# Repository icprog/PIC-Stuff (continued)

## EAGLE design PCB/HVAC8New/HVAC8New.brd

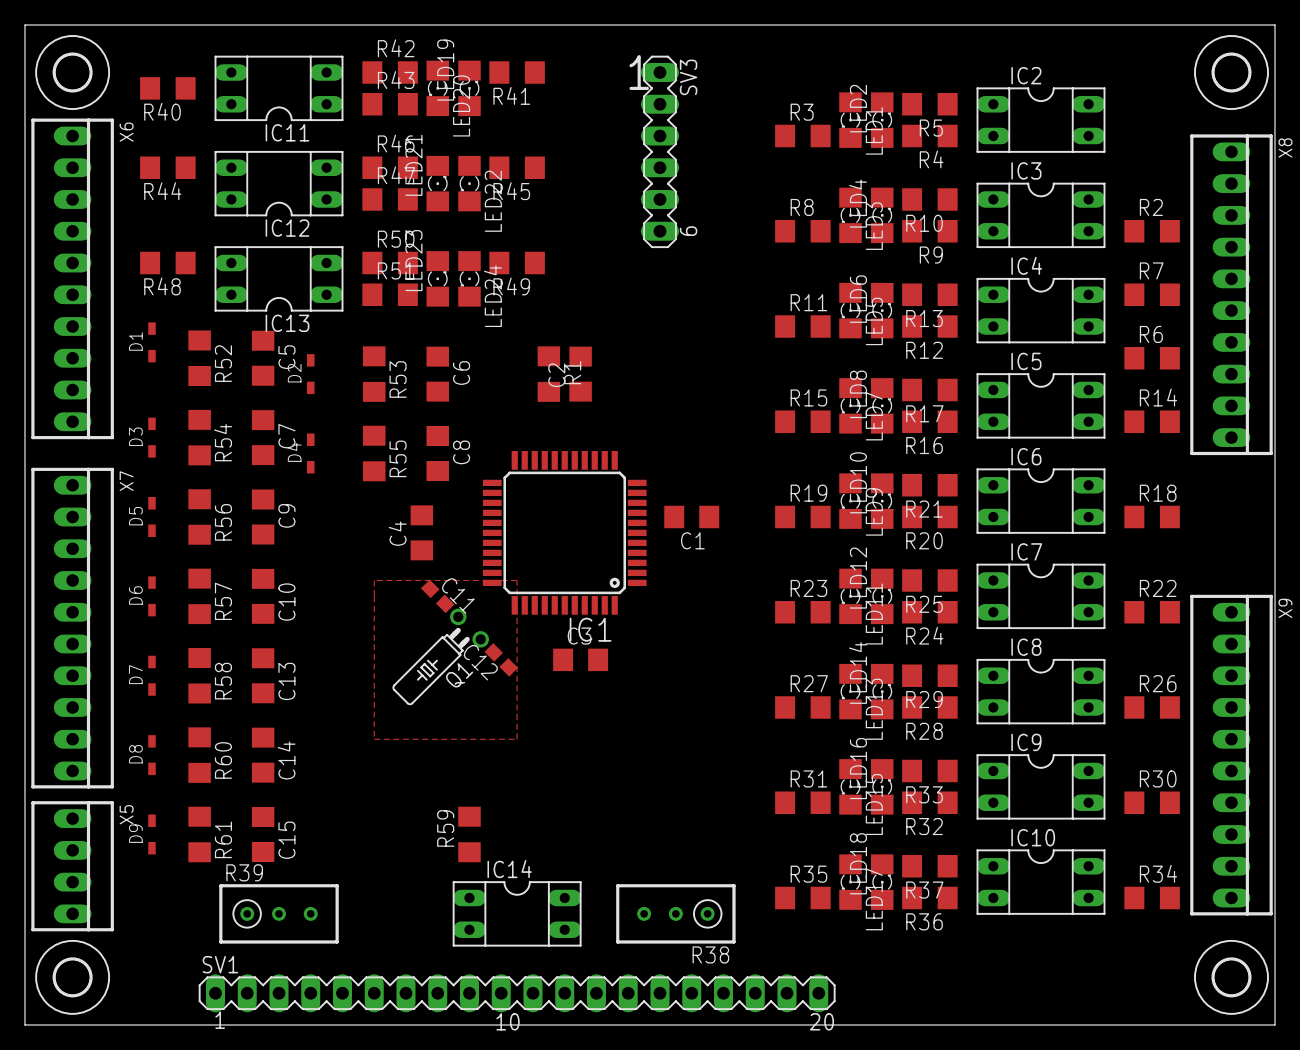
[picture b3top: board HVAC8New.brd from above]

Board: 2 copper layers, 100.0 x 80.0 mm, 135 parts (0 on the bottom side), 104 nets, no tracks yet.

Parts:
C1, C5, C6, C7, C8, C9, C10, C13, C14, C15: 10uf; C1206
C2, C3, C4: .1uf; C1206
C11, C12: 12pf; C0603
D1, D2, D3, D4, D5, D6, D7, D8, D9: 5.1V; SOD323
H1, H2, H3, H4: MOUNT-HOLE2.8; 2,8
IC1: PIC24FV16KM204; TQFP44
IC2, IC3, IC4, IC5, IC6, IC7, IC8, IC9, IC10, IC11, IC12, IC13, IC14: SOCKET-04
LED1, LED3, LED5, LED7, LED9, LED11, LED13, LED15, LED17, LED19, LED21, LED23: Red; LED_1206
LED2, LED4, LED6, LED8, LED10, LED12, LED14, LED16, LED18, LED20, LED22, LED24: Green; LED_1206
Q1: 32.768KHz; TC26H
R1: 10K; R1206
R2, R6, R7, R14, R18, R22, R26, R30, R34, R40, R44, R48: 0R; R1206
R3, R8, R11, R15, R19, R23, R27, R31, R35, R41, R45, R49, R59: 680R; R1206
R4, R5, R9, R10, R12, R13, R16, R17, R20, R21, R24, R25, R28, R29, R32, R33, R36, R37, R42, R43, R46, R47, R50, R51: 330R; R1206
R38, R39: 10K; RTRIM3296W
R52, R53, R54, R55, R56, R57, R58, R60, R61: 250R; R1206
SV1: LCD&Touch; MA20-1
SV3: Program; MA06-1
X5: 22-23-2041
X6, X7, X8, X9: 22-23-2101

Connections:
unnamed: IC13.1, R51.1
unnamed: IC1.18, R1.2, SV3.1
unnamed: IC2.1, R5.1
unnamed: IC1.12, LED7.A, LED8.C, R17.2
unnamed: IC2.4, X8.3
unnamed: LED1.C, LED2.A, R3.2, R4.2
unnamed: IC2.3, R2.1
unnamed: IC3.1, R10.1
unnamed: R2.2, X8.4
unnamed: IC3.4, X8.5
unnamed: LED3.C, LED4.A, R8.2, R9.2
unnamed: IC3.3, R7.1
unnamed: IC11.1, R43.1
unnamed: R7.2, X8.6
unnamed: IC4.1, R13.1
unnamed: LED5.C, LED6.A, R11.2, R12.2
unnamed: IC4.3, R6.1
unnamed: LED19.C, LED20.A, R41.2, R42.2
unnamed: R14.2, X8.10
unnamed: IC5.4, X8.9
unnamed: IC5.1, R17.1
unnamed: LED7.C, LED8.A, R15.2, R16.2
unnamed: IC5.3, R14.1
unnamed: IC6.1, R21.1
unnamed: LED9.C, LED10.A, R19.2, R20.2
unnamed: IC6.3, R18.1
unnamed: R6.2, X8.8
unnamed: IC4.4, X8.7
unnamed: IC11.3, R40.1
unnamed: IC6.4, X9.1
unnamed: R18.2, X9.2
unnamed: IC12.1, R47.1
unnamed: IC7.1, R25.1
unnamed: LED11.C, LED12.A, R23.2, R24.2
unnamed: IC7.3, R22.1
unnamed: IC1.9, LED9.A, LED10.C, R21.2
unnamed: IC7.4, X9.3
unnamed: R22.2, X9.4
unnamed: IC8.1, R29.1
unnamed: LED13.C, LED14.A, R27.2, R28.2
unnamed: IC8.3, R26.1
unnamed: IC9.1, R33.1
unnamed: LED15.C, LED16.A, R31.2, R32.2
unnamed: IC9.3, R30.1
unnamed: IC1.5, LED15.A, LED16.C, R33.2
unnamed: IC1.15, LED19.A, LED20.C, R43.2
unnamed: IC10.1, R37.1
unnamed: LED17.C, LED18.A, R35.2, R36.2
unnamed: IC10.3, R34.1
unnamed: IC1.4, LED17.A, LED18.C, R37.2
unnamed: IC8.4, X9.5
unnamed: R26.2, X9.6
unnamed: IC9.4, X9.7
unnamed: R30.2, X9.8
unnamed: IC10.4, X9.9
unnamed: R34.2, X9.10
unnamed: LED21.C, LED22.A, R45.2, R46.2
unnamed: IC12.3, R44.1
unnamed: IC1.19, LED21.A, LED22.C, R47.2
unnamed: R40.2, X6.1
unnamed: IC1.6, LED13.A, LED14.C, R29.2
unnamed: IC11.4, X6.2
unnamed: R39.2, SV1.3
unnamed: R44.2, X6.3
unnamed: IC12.4, X6.4
unnamed: IC1.3, SV1.6
unnamed: IC1.8, LED11.A, LED12.C, R25.2
unnamed: IC1.2, SV1.4
unnamed: IC1.31, LED1.A, LED2.C, R5.2
unnamed: IC1.13, LED5.A, LED6.C, R13.2
unnamed: IC1.30, LED3.A, LED4.C, R10.2
unnamed: IC1.35, SV1.11
unnamed: IC1.36, SV1.12
unnamed: IC1.37, SV1.13
unnamed: IC1.38, SV1.14
unnamed: IC14.3, SV1.15
unnamed: LED23.C, LED24.A, R49.2, R50.2
unnamed: IC13.3, R48.1
unnamed: IC1.23, LED23.A, LED24.C, R51.2
unnamed: R48.2, X6.5
unnamed: IC13.4, X6.6
unnamed: IC14.4, R38.2
unnamed: C5.2, D1.1, IC1.24, R52.2, X6.8
unnamed: IC1.26, SV1.17
unnamed: C6.2, D2.1, IC1.25, R53.2, X6.10
unnamed: IC1.27, SV1.18
unnamed: C7.2, D3.1, IC1.14, R54.2, X7.2
unnamed: IC1.1, SV1.19
unnamed: C8.2, D4.1, IC1.11, R55.2, X7.4
unnamed: IC1.32, SV1.20
unnamed: IC1.22, SV3.5
unnamed: C9.2, D5.1, IC1.10, R56.2, X7.6
unnamed: C10.2, D6.1, IC1.41, R57.2, X7.8
unnamed: IC1.21, SV3.4
unnamed: C12.2, IC1.34, Q1.1
unnamed: C11.2, IC1.33, Q1.2
unnamed: C13.2, D7.1, IC1.42, R58.2, X7.10
unnamed: IC14.1, R59.1
unnamed: IC1.20, R59.2
unnamed: C14.2, D8.1, IC1.43, R60.2, X5.2
unnamed: C15.2, D9.1, IC1.44, R61.2, X5.4
VDD: C2.2, C3.2, C4.2, IC1.17, IC1.28, IC1.40, R1.1, R3.1, R8.1, R11.1, R15.1, R19.1, R23.1, R27.1, R31.1, R35.1, R38.3, R39.1, R41.1, R45.1, R49.1, SV1.2, SV3.2, X8.1
VDDCORENET: C1.2, IC1.7
VSS: C1.1, C2.1, C3.1, C4.1, C5.1, C6.1, C7.1, C8.1, C9.1, C10.1, C11.1, C12.1, C13.1, C14.1, C15.1, D1.2, D2.2, D3.2, D4.2, D5.2, D6.2, D7.2, D8.2, D9.2, IC1.16, IC1.29, IC1.39, IC2.2, IC3.2, IC4.2, IC5.2, IC6.2, IC7.2, IC8.2, IC9.2, IC10.2, IC11.2, IC12.2, IC13.2, IC14.2, R4.1, R9.1, R12.1, R16.1, R20.1, R24.1, R28.1, R32.1, R36.1, R38.1, R39.3, R42.1, R46.1, R50.1, R52.1, R53.1, R54.1, R55.1, R56.1, R57.1, R58.1, R60.1, R61.1, SV1.1, SV1.5, SV1.7, SV1.8, SV1.9, SV1.10, SV1.16, SV3.3, X5.1, X5.3, X6.7, X6.9, X7.1, X7.3, X7.5, X7.7, X7.9, X8.2

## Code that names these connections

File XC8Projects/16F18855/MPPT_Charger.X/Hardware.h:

/*****************************************************************************
*                           Hardware.h
*
* Description: Hardware related definitions
*
* Hardware:  Synchronous Inverse SEPIC (Zeta) Converter + Battery Charging Library
*
* Resources: PICC 9.83 / MPLAB 8.80
*
******************************************************************************/

#include <xc.h>

// #define _XTAL_FREQ 				16000000                                    //moved to system

#ifndef HARDWARE_H
	#define HARDWARE_H
//	enum LED_MODES { LED_OFF = 100, LED_ON = 101, BLINK_05HZ = 16, BLINK_2HZ = 4 };     // not going to use
#endif

#define		IOUT				RA1
#define		VIN					RA2
#define		IIN					RC2
#define		VOUT				RC3

#define		LED					RC5

//								  76543210
#define		ADCON0_INIT 		0b10000001
#define		ADCON1_INIT  		0b11010000

#define		IOUT_SENSE_CHAN			0x01
#define		VIN_CHAN				0x02
#define		IIN_SENSE_CHAN			0x06
#define		VOUT_CHAN				0x07

#define		FVR_CHAN				0x1F
#define		FVR_MAX					932

#define		SHUNT_VALUE						5		//mOhms
#define		SHUNT_AMPLIFICATION_OUT			106		// should be 101
#define		VOUT_DIVIDER					4
#define		VDD_VAL							5037	//mVolts

#define		NCO_MIN				1
#define		NCO_START			1

#define		NCO_MAX				29500			//app. 450k

#define		NCO_16P				0x80
#define		NCO_32P				0xA0

//#define		WARMUP_TIME			64                                              // moved to BatteryCharger
#define		CURRENT_MODE		4
#define		ERR_MAX				4095
#define		ERR_MIN				-4095

//	For this demo board VDD is 5037mV, IOUT shunt is 5mOhm, IOUT amplification 106, VOUT divider is 4

#define		AD_SAMPLES			4
#define		SAMPLES_AVG			16

#define		AD_SET_CHAN(x)		{ ADCON0 = ADCON0_INIT | (x << 2); }
#define		AD_CONVERT()		{ GO_nDONE = 1; while(GO_nDONE); }
#define		VREF_COMP(x)		{ x = (unsigned int)x * VREF_VDD_MAX / vref; }

#define		STOP_CONVERTER()	{ increment = 0; set_NCO(); TRIS_NCO = 1; }     // moved to BatteryCharger
#define  	START_CONVERTER()	{ warmup = WARMUP_TIME; TRIS_NCO = 0; }         // moved to BatteryCharger

//#define		ISENSE		iout                                                         // moved to BatteryCharger
//#define		VSENSE		vout                                                     // moved to BatteryCharger

//#define		SET_VOLTAGE(x)		{ vref = x; }                               // moved to BatteryCharger
// #define		SET_CURRENT(x)		{ iref = x; }                               // moved to BatteryCharger
#define		SET_LED_BLINK(x)	{ led_state = x; }

//#define		CONSTANT_VOLTAGE	(!cmode)                                    // Moved to charger
//#define		I_BAT_DETECT		16                                          // Moved to Charger

#define		STOUS(x)		{ x -= 1; x = ~x; }
#define		USTOS(x)		{ x = ~x; x += 1; }

#define		BUTTON				RA3

#define		NCO					RA4
#define		TRIS_NCO			TRISA4

#define 	BUTTON_COUNT			61

#define		SECOND_COUNT			976
#define 	SECOND_COUNT_START		999

extern unsigned char temp;
extern unsigned int ad_res;
extern unsigned int iout;
extern unsigned int vout;

extern unsigned char lbut, led_state;
extern unsigned char but_cnt, led_cnt;

extern int increment;

extern unsigned int vref;
extern unsigned int iref;
extern unsigned int warmup;
extern char cmode;
extern unsigned char cc_cv;
extern unsigned int second;

extern int	pp,pi;
extern int er;

void Initialize_Hardware(void);
void Init_Registers(void);
void Shutdown_Peripherals(void);
void Measure_Impedance(void);
void Blink(unsigned char num);
void Delay_ms(unsigned int msec);
void pid(unsigned int feedback, unsigned int setpoint);
void set_NCO(void);
void read_ADC(void);
void cc_cv_mode(void);
unsigned char button_scheme(void);
void led_blink(void);

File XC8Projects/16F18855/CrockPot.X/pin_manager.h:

#ifndef PIN_MANAGER_H
#define PIN_MANAGER_H
/*
#define INPUT   1
#define OUTPUT  0

#define HIGH    1
#define LOW     0

#define ANALOG      1
#define DIGITAL     0

#define PULL_UP_ENABLED      1
#define PULL_UP_DISABLED     0

// get/set RC3 procedures
#define RC3_SetHigh()    do { LATCbits.LATC3 = 1; } while(0)
#define RC3_SetLow()   do { LATCbits.LATC3 = 0; } while(0)
#define RC3_Toggle()   do { LATCbits.LATC3 = ~LATCbits.LATC3; } while(0)
#define RC3_GetValue()         PORTCbits.RC3
#define RC3_SetDigitalInput()   do { TRISCbits.TRISC3 = 1; } while(0)
#define RC3_SetDigitalOutput()  do { TRISCbits.TRISC3 = 0; } while(0)
#define RC3_SetPullup()     do { WPUCbits.WPUC3 = 1; } while(0)
#define RC3_ResetPullup()   do { WPUCbits.WPUC3 = 0; } while(0)
#define RC3_SetAnalogMode() do { ANSELCbits.ANSC3 = 1; } while(0)
#define RC3_SetDigitalMode()do { ANSELCbits.ANSC3 = 0; } while(0)

// get/set RC4 procedures
#define RC4_SetHigh()    do { LATCbits.LATC4 = 1; } while(0)
#define RC4_SetLow()   do { LATCbits.LATC4 = 0; } while(0)
#define RC4_Toggle()   do { LATCbits.LATC4 = ~LATCbits.LATC4; } while(0)
#define RC4_GetValue()         PORTCbits.RC4
#define RC4_SetDigitalInput()   do { TRISCbits.TRISC4 = 1; } while(0)
#define RC4_SetDigitalOutput()  do { TRISCbits.TRISC4 = 0; } while(0)
#define RC4_SetPullup()     do { WPUCbits.WPUC4 = 1; } while(0)
#define RC4_ResetPullup()   do { WPUCbits.WPUC4 = 0; } while(0)
#define RC4_SetAnalogMode() do { ANSELCbits.ANSC4 = 1; } while(0)
#define RC4_SetDigitalMode()do { ANSELCbits.ANSC4 = 0; } while(0)

// get/set RC5 procedures
#define RC5_SetHigh()    do { LATCbits.LATC5 = 1; } while(0)
#define RC5_SetLow()   do { LATCbits.LATC5 = 0; } while(0)
#define RC5_Toggle()   do { LATCbits.LATC5 = ~LATCbits.LATC5; } while(0)
#define RC5_GetValue()         PORTCbits.RC5
#define RC5_SetDigitalInput()   do { TRISCbits.TRISC5 = 1; } while(0)
#define RC5_SetDigitalOutput()  do { TRISCbits.TRISC5 = 0; } while(0)
#define RC5_SetPullup()     do { WPUCbits.WPUC5 = 1; } while(0)
#define RC5_ResetPullup()   do { WPUCbits.WPUC5 = 0; } while(0)
#define RC5_SetAnalogMode() do { ANSELCbits.ANSC5 = 1; } while(0)
#define RC5_SetDigitalMode()do { ANSELCbits.ANSC5 = 0; } while(0)

// get/set RC6 procedures
#define RC6_SetHigh()    do { LATCbits.LATC6 = 1; } while(0)
#define RC6_SetLow()   do { LATCbits.LATC6 = 0; } while(0)
#define RC6_Toggle()   do { LATCbits.LATC6 = ~LATCbits.LATC6; } while(0)
#define RC6_GetValue()         PORTCbits.RC6
#define RC6_SetDigitalInput()   do { TRISCbits.TRISC6 = 1; } while(0)
#define RC6_SetDigitalOutput()  do { TRISCbits.TRISC6 = 0; } while(0)
#define RC6_SetPullup()     do { WPUCbits.WPUC6 = 1; } while(0)
#define RC6_ResetPullup()   do { WPUCbits.WPUC6 = 0; } while(0)
#define RC6_SetAnalogMode() do { ANSELCbits.ANSC6 = 1; } while(0)
#define RC6_SetDigitalMode()do { ANSELCbits.ANSC6 = 0; } while(0)

*/

void PIN_MANAGER_Initialize (void);


#endif

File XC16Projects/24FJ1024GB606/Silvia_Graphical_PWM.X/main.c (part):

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
// *************** Inputs ****************************************************************************************************************************************
#define power                   1                                            // Power Switch Input G             
//#define power                   _RG9                                            // Power Switch Input G             
#define steamSwitch             _RB5                                            // Steam Switch Input G
#define brewSwitch              _RB4                                            // Brew Switch Input G
#define waterSwitch             _RB3                                            // Water Switch Input G
// ***************************************************************************************************************************************************************

//***************************Timer2 set in pwm.c
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
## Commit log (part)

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2017-08-27 DONE!
2017-08-28 AtOrd
2017-08-28 Sent
2017-09-09 PID Added
2017-09-10 test
2017-09-12 start
2017-09-15 touch
2017-09-17 fixed early Start on HVACBlue
2017-09-18 Fixed Extended Start Time issue
2017-09-20 Flsh?
2017-09-20 rfee
2017-09-23 RTCC working
2017-09-24 cl w
2017-09-26 Working 5110
2017-10-11 OC-W!!
2017-10-14 updt hvb
2017-10-15 PWM DONE!!
2017-10-29 fix fh
2017-10-31 tehu
2017-11-01 Minor Optimizations
2017-11-01 In Temps Working
2017-11-03 Init Vars
2017-11-10 Manual_Update
2017-11-17 NewBlue2
2017-11-18 blue2
2017-12-05 Comment Updates
2017-12-18 working?
2017-12-18 group not shutting off fixed
2017-12-23 Menu changes
2018-01-03 Add a few devices, to ensure en=verything is turned off by power swicch
2018-02-21 F,gl
2018-02-26 tuff
2018-02-26 fuck!!!!!
2018-02-26 fucken junk
    fuck
2018-02-26 AFin
2018-02-26 JunkFinished
2018-02-26 JunkFinallyDone
2018-02-28 actfin
2018-02-28 FinishedForSure
2018-03-01 Really,really final
2018-03-06 NothingYet
2018-03-09 docs
2018-03-09 Backlight disabled
2018-03-12 del dup
2018-03-20 Start Over with BBQ Controller
2018-03-21 fsfu
2018-03-24 turn Bl on
2018-03-29 TimsStuff
2018-03-29 dsdl
2018-03-30 udCf
2018-03-30 rtcc
2018-03-31 DataSheetsUploads
2018-03-31 OpenLidDetectionAdded
2018-04-01 OpenLidDetection
2018-04-01 Update Lid Open Time
2018-04-05 Added Settings Menu(untested)
2018-04-05 Minor Cleanup
2018-04-05 Fix Setting Menu
2018-04-06 More Menu Clean-up
2018-04-07 BC on 24FJ1024
2018-04-10 LCD Code Cleanup
2018-04-10 Datasheet Updates
2018-04-10 Add PWM Backlight control
2018-04-11 Backlight Adjust Display
2018-04-11 Added some SPI Stuff
2018-04-13 Bunch o shit
2018-04-21 text changes
2018-04-30 Files
2018-05-01 BuckInfo
2018-05-03 MPPT Stuff
2018-05-05 3.3VoltPICUpdate
2018-05-06 Minor tweaks
2018-05-07 nothing
2018-05-11 Added readAnalogs
2018-05-12 Modify PID Algorithm rather substantially! (How it should work?)
2018-05-13 Big re-work of the Integral part of the PID algorithm
2018-05-13 Change Sample size
2018-05-15 Start of Eagle MPPT
2018-05-15 ripup
2018-05-18 Start of Board Design
2018-05-18 progress
2018-05-23 gfcr
2018-05-25 NFpRW
2018-05-29 SendOutForFab
2018-06-01 PID Code Modification
2018-06-10 decrease integral action
2018-06-15 woit
2018-06-15 cler
2018-06-22 junk
2018-06-22 Close on 1 Channel
2018-06-24 newIdea
2018-06-26 Added Cooling Fan
2018-06-29 added D term
2018-06-29 Corrected PID Adjustments
2018-06-30 Moved Fault Reset to the Power supply for the ACS711, just reset the ACS711 rather than the whole processor
2018-06-30 Nothing at all
2018-06-30 also, nothing
2018-07-01 fuckAll
2018-07-05 DUdt
2018-07-05 LCD adjust
2018-07-06 Stuff
2018-07-12 Initial Commit
    12V MPPT Solar Charger, being used over for a 24V system
2018-07-13 Adjust 24V Settings
2018-07-14 Fan Not Working
2018-07-19 fix fucked up DO
2018-08-09 Tuning
2018-08-13 Re-do PID Algorithm
2018-08-17 Add second Channel
2018-08-18 Cleanup
2018-08-27 initial
2018-08-31 Upload Tims Stuff
2018-09-11 Minor Changes
2018-09-13 tune MPPT voltage adjustment
2018-09-14 Changes from other Repo
2018-10-17 nthng
2018-10-23 Datasheets
